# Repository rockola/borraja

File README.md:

borraja
================

Alembic Stratoblaster

* v0.1: initial revision, unverified

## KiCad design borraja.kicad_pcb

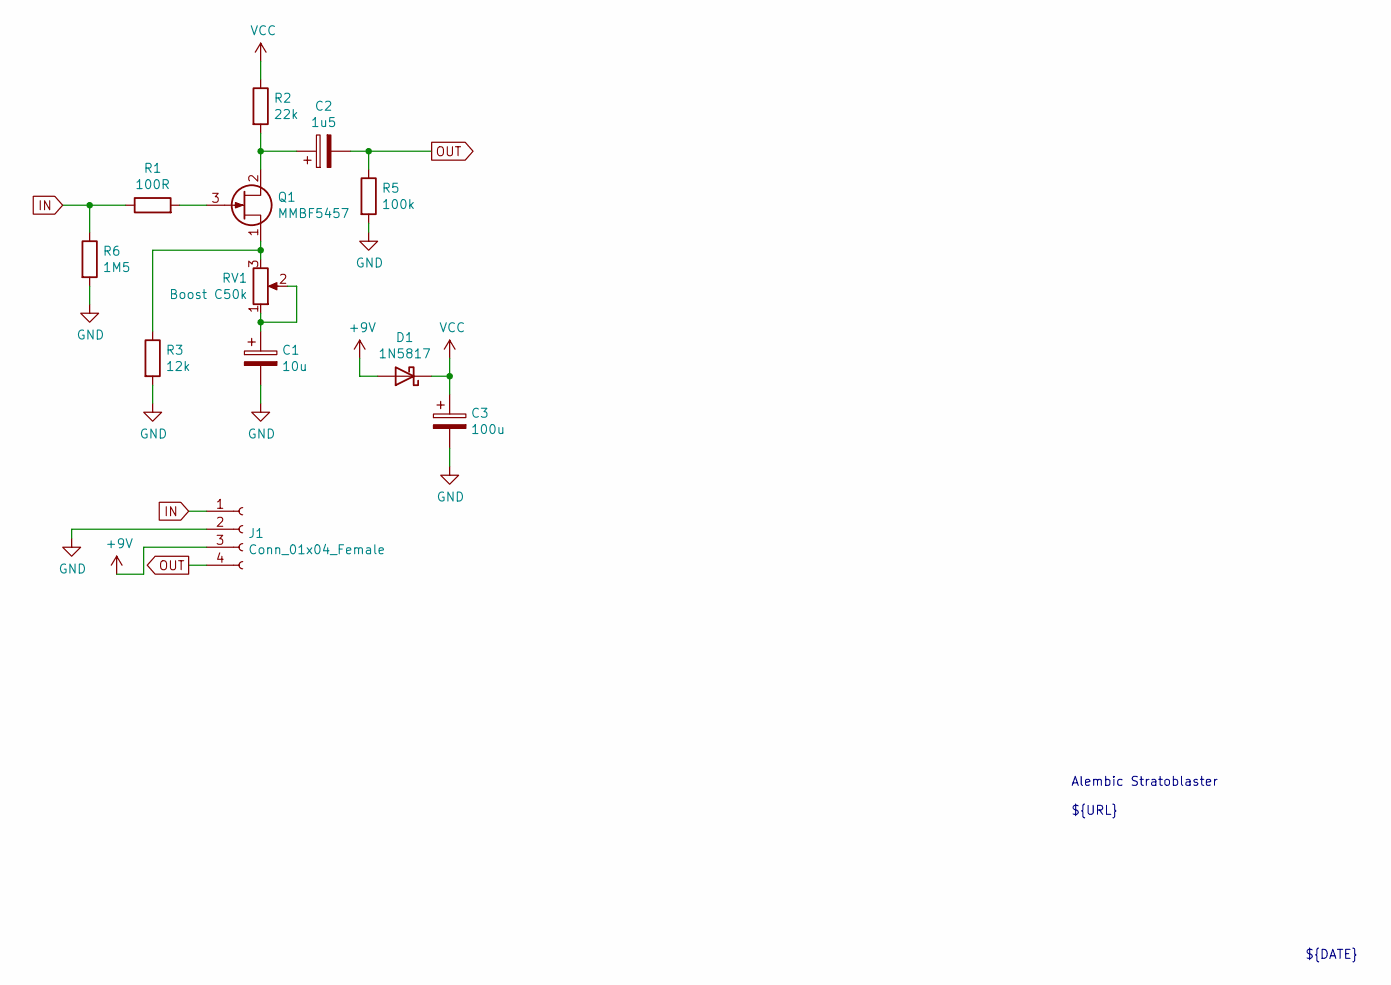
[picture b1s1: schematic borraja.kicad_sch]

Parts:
C1: 10u; CP_D5.0_P2.50
C2: 1u5; CP_D5.0_P2.50
C3: 100u; CP_D6.3_P2.50
D1: 1N5817; D_DO-41_SOD81_P10.16mm_Horizontal
J1: Conn_01x04_Female; Stomp_4pin_Power_No_LED
Q1: MMBF5457; SOT-23
R1: 100R; R_0603_1608Metric
R2: 22k; R_0603_1608Metric
R3: 12k; R_0603_1608Metric
R5: 100k; R_0603_1608Metric
R6: 1M5; R_0603_1608Metric
RV1: Boost C50k; 16MM_B.MOUNT

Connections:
+9V: D1.2 (A), J1.3
GND: C1.2, C3.2, J1.2, R3.2, R5.2, R6.2
IN: J1.1, R1.1, R6.1
unnamed: C1.1, RV1.1, RV1.2
unnamed: Q1.3 (G), R1.2
unnamed: C2.1, Q1.2 (S), R2.2
unnamed: Q1.1 (D), R3.1, RV1.3
OUT: C2.2, J1.4, R5.1
VCC: C3.1, D1.1 (K), R2.1

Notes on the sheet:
Alembic Stratoblaster ${URL}
${TITLE}
${DATE}
${REVISION}

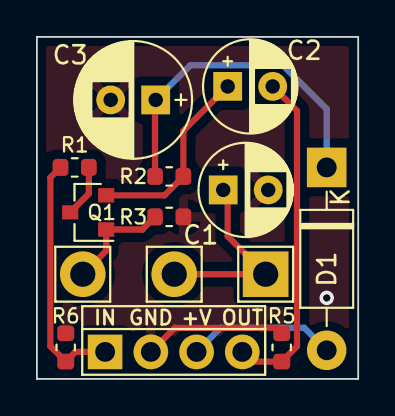
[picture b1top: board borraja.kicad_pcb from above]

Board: 2 copper layers, 17.8 x 19.0 mm, 12 parts (0 on the bottom side), 9 nets.

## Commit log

2020-12-04 ignores
2020-12-04 v0.1: initial rev, Gerbers sent to Oshpark
2020-12-04 v0.1 schematic
2020-12-04 fix: schem url
2022-01-11 updated to KiCad 6.0
